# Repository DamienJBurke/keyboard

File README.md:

# keyboard
Repo for my keyboard Design schematic and pcb layout

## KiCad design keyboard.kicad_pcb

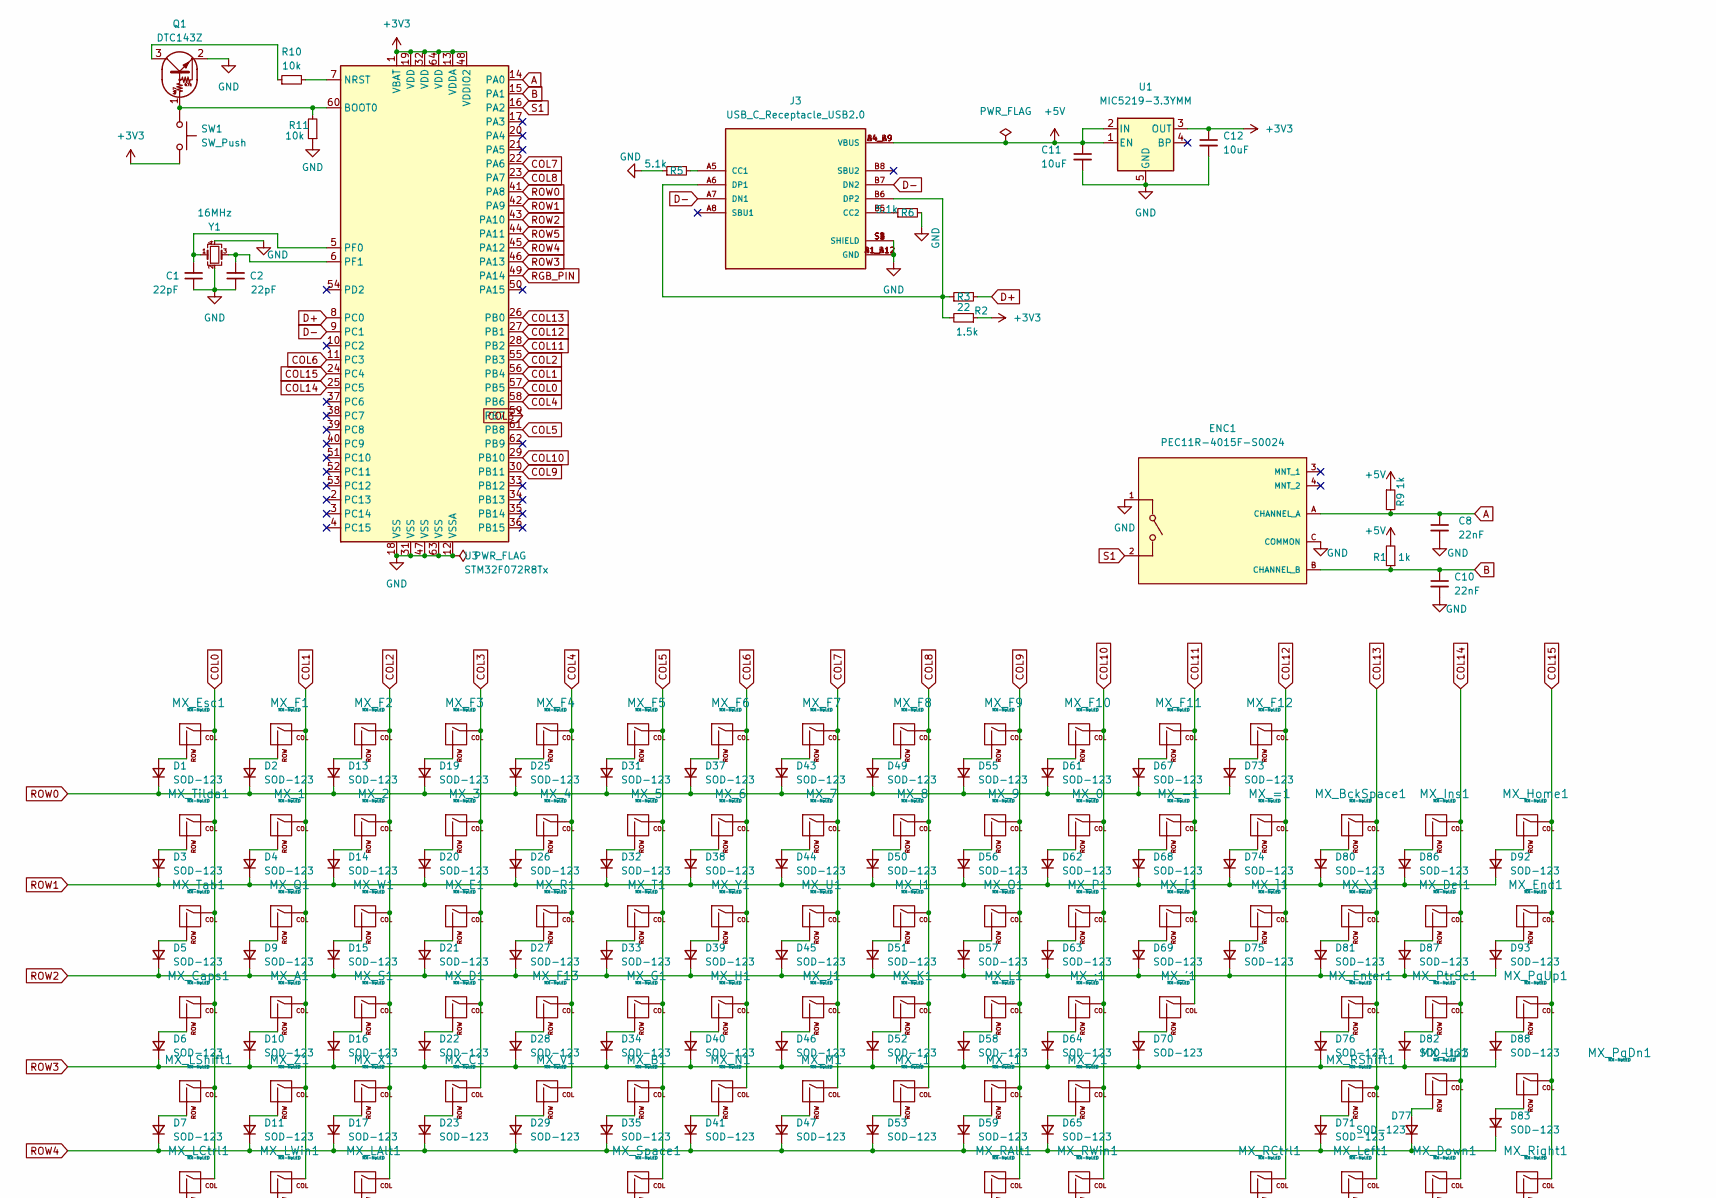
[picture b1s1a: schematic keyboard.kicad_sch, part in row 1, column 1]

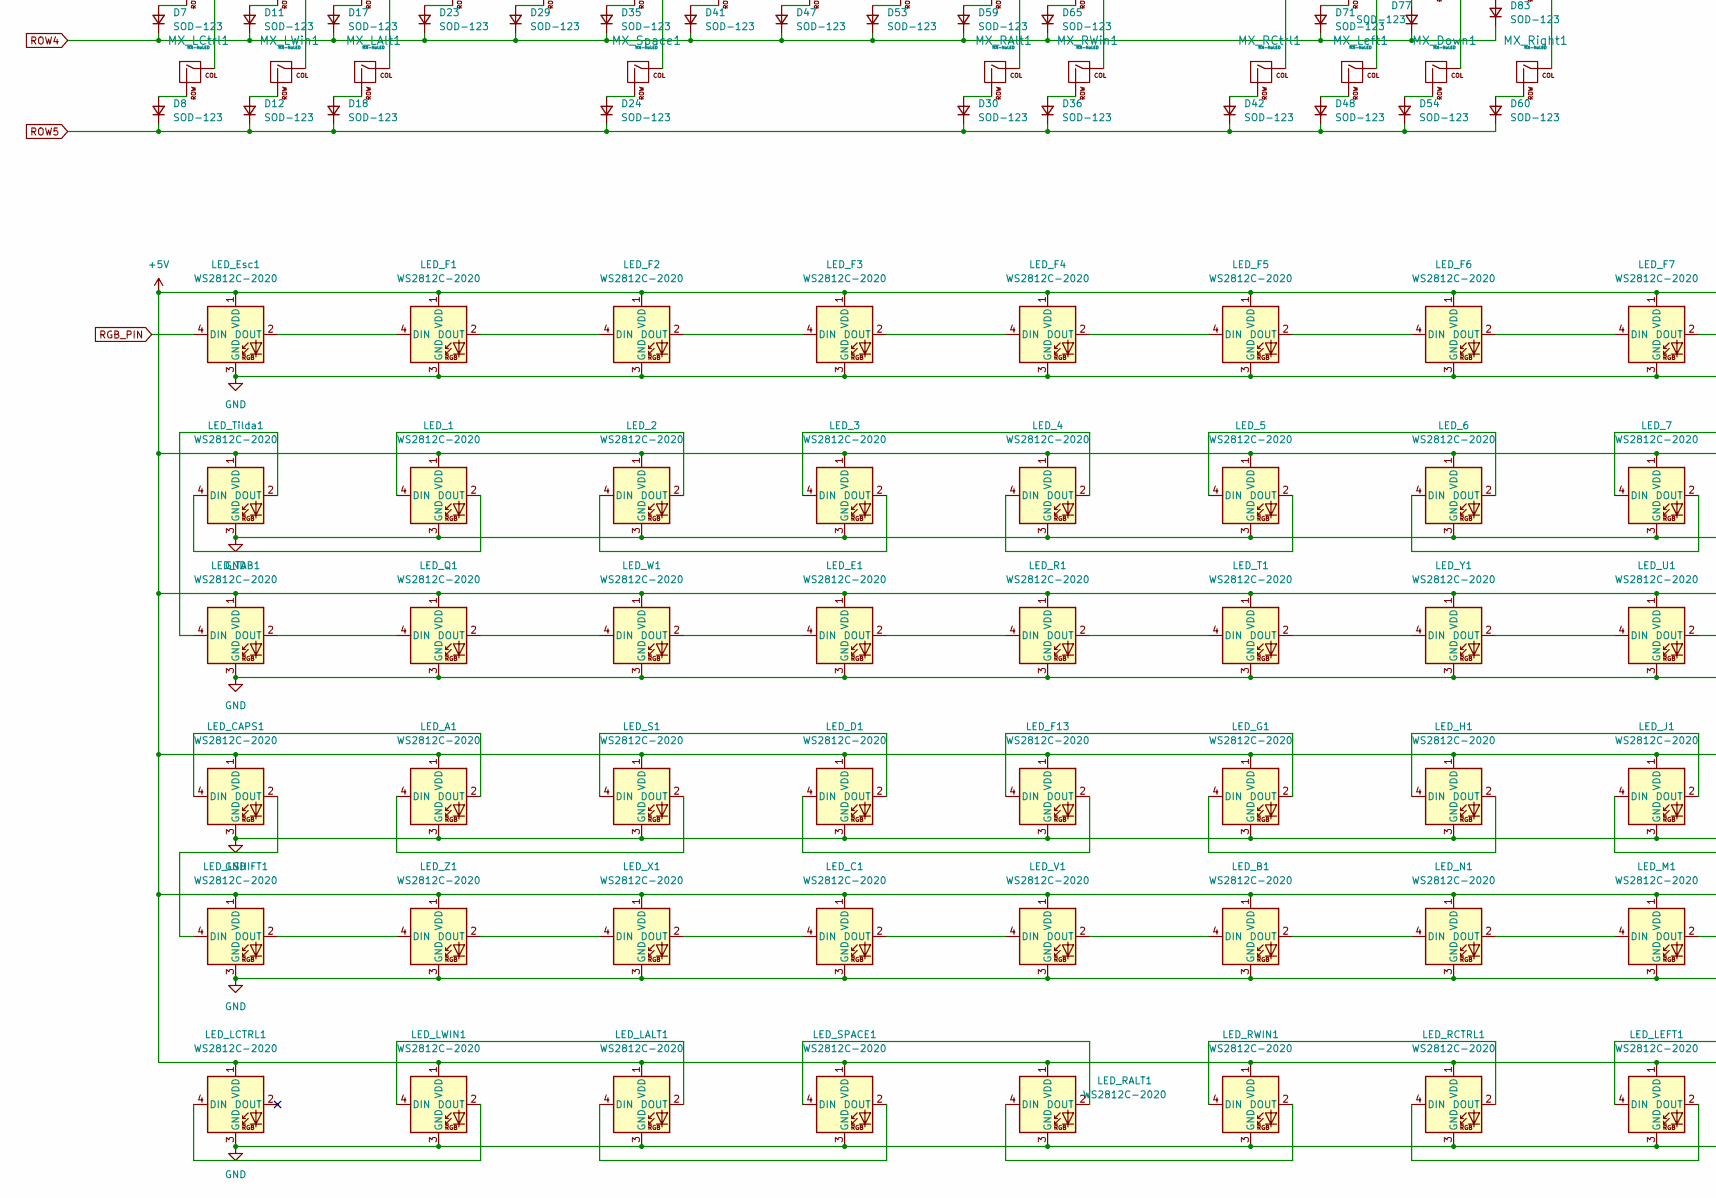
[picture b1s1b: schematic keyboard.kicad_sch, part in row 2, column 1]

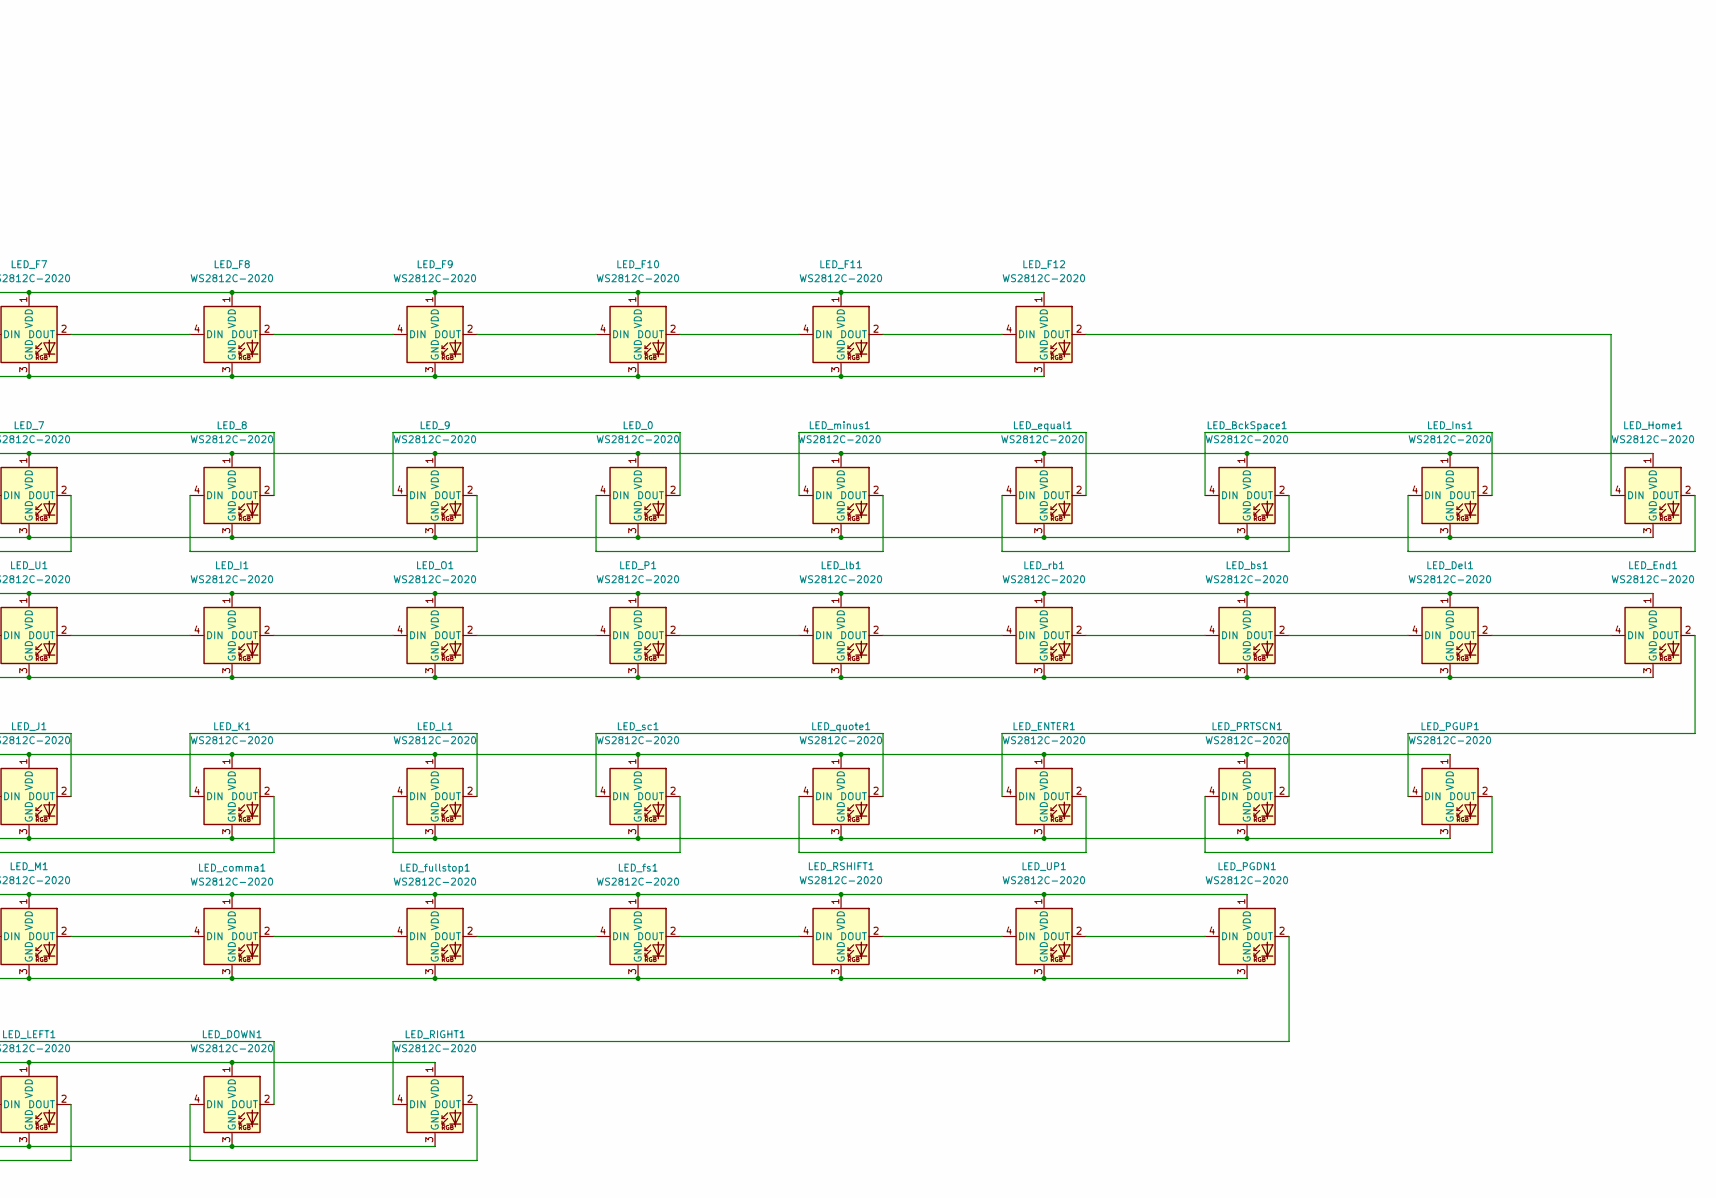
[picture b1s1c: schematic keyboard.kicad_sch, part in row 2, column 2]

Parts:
C1, C2: 22pF; C_0805_2012Metric
C8, C10: 22nF; C_0805_2012Metric
C11, C12: 10uF; C_0805_2012Metric
D1, D2, D3, D4, D5, D6, D7, D8, D9, D10, D11, D12, D13, D14, D15, D16, D17, D18, D19, D20, D21, D22, D23, D24, D25, D26, D27, D28, D29, D30, D31, D32, D33, D34, D35, D36, D37, D38, D39, D40, D41, D42, D43, D44, D45, D46, D47, D48, D49, D50, D51, D52, D53, D54, D55, D56, D57, D58, D59, D60, D61, D62, D63, D64, D65, D67, D68, D69, D70, D71, D73, D74, D75, D76, D77, D80, D81, D82, D83, D86, D87, D88, D92, D93: SOD-123; D_SOD-123
ENC1: PEC11R-4015F-S0024; XDCR_PEC11R-4215F-S0024; current rating 10mA; voltage rating DC 5V; mouser part number 652-PEC11R-4015F-S24; digikey description ROTARY ENCODER MECHANICAL 24PPR
J3: USB_C_Receptacle_USB2.0; HRO_TYPE-C-31-M-12; PARTREV 2020.12.08
LED_0, LED_1, LED_2, LED_3, LED_4, LED_5, LED_6, LED_7, LED_8, LED_9: WS2812C-2020; SK6812-MINI-E-CUSTOM; PARTREV V1.0
LED_A1: WS2812C-2020; SK6812-MINI-E-CUSTOM; PARTREV V1.0
LED_B1: WS2812C-2020; SK6812-MINI-E-CUSTOM; PARTREV V1.0
LED_BckSpace1: WS2812C-2020; SK6812-MINI-E-CUSTOM; PARTREV V1.0
LED_C1: WS2812C-2020; SK6812-MINI-E-CUSTOM; PARTREV V1.0
LED_CAPS1: WS2812C-2020; SK6812-MINI-E-CUSTOM; PARTREV V1.0
LED_D1: WS2812C-2020; SK6812-MINI-E-CUSTOM; PARTREV V1.0
LED_DOWN1: WS2812C-2020; SK6812-MINI-E-CUSTOM; PARTREV V1.0
LED_Del1: WS2812C-2020; SK6812-MINI-E-CUSTOM; PARTREV V1.0
LED_E1: WS2812C-2020; SK6812-MINI-E-CUSTOM; PARTREV V1.0
LED_ENTER1: WS2812C-2020; SK6812-MINI-E-CUSTOM; PARTREV V1.0
LED_End1: WS2812C-2020; SK6812-MINI-E-CUSTOM; PARTREV V1.0
LED_Esc1: WS2812C-2020; SK6812-MINI-E-CUSTOM; PARTREV V1.0
LED_F1, LED_F2, LED_F3, LED_F4, LED_F5, LED_F6, LED_F7, LED_F8, LED_F9, LED_F10, LED_F11, LED_F12, LED_F13: WS2812C-2020; SK6812-MINI-E-CUSTOM; PARTREV V1.0
LED_G1: WS2812C-2020; SK6812-MINI-E-CUSTOM; PARTREV V1.0
LED_H1: WS2812C-2020; SK6812-MINI-E-CUSTOM; PARTREV V1.0
LED_Home1: WS2812C-2020; SK6812-MINI-E-CUSTOM; PARTREV V1.0
LED_I1: WS2812C-2020; SK6812-MINI-E-CUSTOM; PARTREV V1.0
LED_Ins1: WS2812C-2020; SK6812-MINI-E-CUSTOM; PARTREV V1.0
LED_J1: WS2812C-2020; SK6812-MINI-E-CUSTOM; PARTREV V1.0
LED_K1: WS2812C-2020; SK6812-MINI-E-CUSTOM; PARTREV V1.0
LED_L1: WS2812C-2020; SK6812-MINI-E-CUSTOM; PARTREV V1.0
LED_LALT1: WS2812C-2020; SK6812-MINI-E-CUSTOM; PARTREV V1.0
LED_LCTRL1: WS2812C-2020; SK6812-MINI-E-CUSTOM; PARTREV V1.0
LED_LEFT1: WS2812C-2020; SK6812-MINI-E-CUSTOM; PARTREV V1.0
LED_LSHIFT1: WS2812C-2020; SK6812-MINI-E-CUSTOM; PARTREV V1.0
LED_LWIN1: WS2812C-2020; SK6812-MINI-E-CUSTOM; PARTREV V1.0
LED_M1: WS2812C-2020; SK6812-MINI-E-CUSTOM; PARTREV V1.0
LED_N1: WS2812C-2020; SK6812-MINI-E-CUSTOM; PARTREV V1.0
LED_O1: WS2812C-2020; SK6812-MINI-E-CUSTOM; PARTREV V1.0
LED_P1: WS2812C-2020; SK6812-MINI-E-CUSTOM; PARTREV V1.0
LED_PGDN1: WS2812C-2020; SK6812-MINI-E-CUSTOM; PARTREV V1.0
LED_PGUP1: WS2812C-2020; SK6812-MINI-E-CUSTOM; PARTREV V1.0
LED_PRTSCN1: WS2812C-2020; SK6812-MINI-E-CUSTOM; PARTREV V1.0
LED_Q1: WS2812C-2020; SK6812-MINI-E-CUSTOM; PARTREV V1.0
LED_R1: WS2812C-2020; SK6812-MINI-E-CUSTOM; PARTREV V1.0
LED_RALT1: WS2812C-2020; SK6812-MINI-E-CUSTOM; PARTREV V1.0
LED_RCTRL1: WS2812C-2020; SK6812-MINI-E-CUSTOM; PARTREV V1.0
LED_RIGHT1: WS2812C-2020; SK6812-MINI-E-CUSTOM; PARTREV V1.0
LED_RSHIFT1: WS2812C-2020; SK6812-MINI-E-CUSTOM; PARTREV V1.0
LED_RWIN1: WS2812C-2020; SK6812-MINI-E-CUSTOM; PARTREV V1.0
LED_S1: WS2812C-2020; SK6812-MINI-E-CUSTOM; PARTREV V1.0
LED_SPACE1: WS2812C-2020; SK6812-MINI-E-CUSTOM; PARTREV V1.0
LED_T1: WS2812C-2020; SK6812-MINI-E-CUSTOM; PARTREV V1.0
LED_TAB1: WS2812C-2020; SK6812-MINI-E-CUSTOM; PARTREV V1.0
LED_Tilda1: WS2812C-2020; SK6812-MINI-E-CUSTOM; PARTREV V1.0
LED_U1: WS2812C-2020; SK6812-MINI-E-CUSTOM; PARTREV V1.0
LED_UP1: WS2812C-2020; SK6812-MINI-E-CUSTOM; PARTREV V1.0
LED_V1: WS2812C-2020; SK6812-MINI-E-CUSTOM; PARTREV V1.0
LED_W1: WS2812C-2020; SK6812-MINI-E-CUSTOM; PARTREV V1.0
LED_X1: WS2812C-2020; SK6812-MINI-E-CUSTOM; PARTREV V1.0
LED_Y1: WS2812C-2020; SK6812-MINI-E-CUSTOM; PARTREV V1.0
LED_Z1: WS2812C-2020; SK6812-MINI-E-CUSTOM; PARTREV V1.0
LED_bs1: WS2812C-2020; SK6812-MINI-E-CUSTOM; PARTREV V1.0
LED_comma1: WS2812C-2020; SK6812-MINI-E-CUSTOM; PARTREV V1.0
LED_equal1: WS2812C-2020; SK6812-MINI-E-CUSTOM; PARTREV V1.0
LED_fs1: WS2812C-2020; SK6812-MINI-E-CUSTOM; PARTREV V1.0
LED_fullstop1: WS2812C-2020; SK6812-MINI-E-CUSTOM; PARTREV V1.0
LED_lb1: WS2812C-2020; SK6812-MINI-E-CUSTOM; PARTREV V1.0
LED_minus1: WS2812C-2020; SK6812-MINI-E-CUSTOM; PARTREV V1.0
LED_quote1: WS2812C-2020; SK6812-MINI-E-CUSTOM; PARTREV V1.0
LED_rb1: WS2812C-2020; SK6812-MINI-E-CUSTOM; PARTREV V1.0
LED_sc1: WS2812C-2020; SK6812-MINI-E-CUSTOM; PARTREV V1.0
MX_0, MX_1, MX_2, MX_3, MX_4, MX_5, MX_6, MX_7, MX_8, MX_9, MX_.1: MX-NoLED; SW_Cherry_MX_PCB_1.00u
MX_'1: MX-NoLED; SW_Cherry_MX_PCB_1.00u
MX_,1: MX-NoLED; SW_Cherry_MX_PCB_1.00u
MX_-1: MX-NoLED; SW_Cherry_MX_PCB_1.00u
MX_/1: MX-NoLED; SW_Cherry_MX_PCB_1.00u
MX_;1: MX-NoLED; SW_Cherry_MX_PCB_1.00u
MX_=1: MX-NoLED; SW_Cherry_MX_PCB_1.00u
MX_A1: MX-NoLED; SW_Cherry_MX_PCB_1.00u
MX_B1: MX-NoLED; SW_Cherry_MX_PCB_1.00u
MX_BckSpace1: MX-NoLED; Cherry 2u with stablizer
MX_C1: MX-NoLED; SW_Cherry_MX_PCB_1.00u
MX_Caps1: MX-NoLED; SW_Cherry_MX_PCB_1.75u
MX_D1: MX-NoLED; SW_Cherry_MX_PCB_1.00u
MX_Del1: MX-NoLED; SW_Cherry_MX_PCB_1.00u
MX_Down1: MX-NoLED; SW_Cherry_MX_PCB_1.00u
MX_E1: MX-NoLED; SW_Cherry_MX_PCB_1.00u
MX_End1: MX-NoLED; SW_Cherry_MX_PCB_1.00u
MX_Enter1: MX-NoLED; Cherry 2.25 with stablizer
MX_Esc1: MX-NoLED; SW_Cherry_MX_PCB_1.00u
MX_F1, MX_F2, MX_F3, MX_F4, MX_F5, MX_F6, MX_F7, MX_F8, MX_F9, MX_F10, MX_F11, MX_F12, MX_F13: MX-NoLED; SW_Cherry_MX_PCB_1.00u
MX_G1: MX-NoLED; SW_Cherry_MX_PCB_1.00u
MX_H1: MX-NoLED; SW_Cherry_MX_PCB_1.00u
MX_Home1: MX-NoLED; SW_Cherry_MX_PCB_1.00u
MX_I1: MX-NoLED; SW_Cherry_MX_PCB_1.00u
MX_Ins1: MX-NoLED; SW_Cherry_MX_PCB_1.00u
MX_J1: MX-NoLED; SW_Cherry_MX_PCB_1.00u
MX_K1: MX-NoLED; SW_Cherry_MX_PCB_1.00u
MX_L1: MX-NoLED; SW_Cherry_MX_PCB_1.00u
MX_LAlt1: MX-NoLED; SW_Cherry_MX_PCB_1.25u
MX_LCtrl1: MX-NoLED; SW_Cherry_MX_PCB_1.25u
MX_LShift1: MX-NoLED; Cherry 2.25 with stablizer
MX_LWin1: MX-NoLED; SW_Cherry_MX_PCB_1.25u
MX_Left1: MX-NoLED; SW_Cherry_MX_PCB_1.00u
MX_M1: MX-NoLED; SW_Cherry_MX_PCB_1.00u
MX_N1: MX-NoLED; SW_Cherry_MX_PCB_1.00u
MX_O1: MX-NoLED; SW_Cherry_MX_PCB_1.00u
MX_P1: MX-NoLED; SW_Cherry_MX_PCB_1.00u
MX_PgDn1: MX-NoLED; SW_Cherry_MX_PCB_1.00u
MX_PgUp1: MX-NoLED; SW_Cherry_MX_PCB_1.00u
MX_PtrSc1: MX-NoLED; SW_Cherry_MX_PCB_1.00u
MX_Q1: MX-NoLED; SW_Cherry_MX_PCB_1.00u
MX_R1: MX-NoLED; SW_Cherry_MX_PCB_1.00u
MX_RAlt1: MX-NoLED; SW_Cherry_MX_PCB_1.25u
MX_RCtrl1: MX-NoLED; SW_Cherry_MX_PCB_1.25u
MX_RShift1: MX-NoLED; Cherry 2.75 with stablizer
MX_RWin1: MX-NoLED; SW_Cherry_MX_PCB_1.25u
MX_Right1: MX-NoLED; SW_Cherry_MX_PCB_1.00u
MX_S1: MX-NoLED; SW_Cherry_MX_PCB_1.00u
MX_Space1: MX-NoLED; Cherry 6u with upside down Stablizer
MX_T1: MX-NoLED; SW_Cherry_MX_PCB_1.00u
MX_Tab1: MX-NoLED; SW_Cherry_MX_PCB_1.50u
MX_Tilda1: MX-NoLED; SW_Cherry_MX_PCB_1.00u
MX_U1: MX-NoLED; SW_Cherry_MX_PCB_1.00u
MX_Up1: MX-NoLED; SW_Cherry_MX_PCB_1.00u
MX_V1: MX-NoLED; SW_Cherry_MX_PCB_1.00u
MX_W1: MX-NoLED; SW_Cherry_MX_PCB_1.00u
MX_X1: MX-NoLED; SW_Cherry_MX_PCB_1.00u
MX_Y1: MX-NoLED; SW_Cherry_MX_PCB_1.00u
MX_Z1: MX-NoLED; SW_Cherry_MX_PCB_1.00u
MX_[1: MX-NoLED; SW_Cherry_MX_PCB_1.00u
MX_\1: MX-NoLED; SW_Cherry_MX_PCB_1.50u
MX_]1: MX-NoLED; SW_Cherry_MX_PCB_1.00u
Q1: DTC143Z; SOTFL3P40_120X120X55L30X32N
R1, R9: 1k; R_0805_2012Metric
R2: 1.5k; R_0805_2012Metric
R3: 22; R_0805_2012Metric
R5, R6: 5.1k; R_0805_2012Metric
R10, R11: 10k; R_0805_2012Metric
SW1: SW_Push; SKQG-1155865
U1: MIC5219-3.3YMM; SOP65P490X110-8N
U3: STM32F072R8Tx; LQFP-64_10x10mm_P0.5mm
Y1: 16MHz; Crystal_SMD_3225-4Pin_3.2x2.5mm

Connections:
+3V3: C12.1, R2.1, SW1.2, U1.3 (OUT), U3.1 (VBAT), U3.13 (VDDA), U3.19 (VDD), U3.32 (VDD), U3.48 (VDDIO2), U3.64 (VDD)
+5V: C11.1, J3.A4_B9 (VBUS), J3.B4_A9 (VBUS), LED_0.1 (VDD), LED_1.1 (VDD), LED_2.1 (VDD), LED_3.1 (VDD), LED_4.1 (VDD), LED_5.1 (VDD), LED_6.1 (VDD), LED_7.1 (VDD), LED_8.1 (VDD), LED_9.1 (VDD), LED_A1.1 (VDD), LED_B1.1 (VDD), LED_BckSpace1.1 (VDD), LED_C1.1 (VDD), LED_CAPS1.1 (VDD), LED_D1.1 (VDD), LED_DOWN1.1 (VDD), LED_Del1.1 (VDD), LED_E1.1 (VDD), LED_ENTER1.1 (VDD), LED_End1.1 (VDD), LED_Esc1.1 (VDD), LED_F1.1 (VDD), LED_F2.1 (VDD), LED_F3.1 (VDD), LED_F4.1 (VDD), LED_F5.1 (VDD), LED_F6.1 (VDD), LED_F7.1 (VDD), LED_F8.1 (VDD), LED_F9.1 (VDD), LED_F10.1 (VDD), LED_F11.1 (VDD), LED_F12.1 (VDD), LED_F13.1 (VDD), LED_G1.1 (VDD), LED_H1.1 (VDD), LED_Home1.1 (VDD), LED_I1.1 (VDD), LED_Ins1.1 (VDD), LED_J1.1 (VDD), LED_K1.1 (VDD), LED_L1.1 (VDD), LED_LALT1.1 (VDD), LED_LCTRL1.1 (VDD), LED_LEFT1.1 (VDD), LED_LSHIFT1.1 (VDD), LED_LWIN1.1 (VDD), LED_M1.1 (VDD), LED_N1.1 (VDD), LED_O1.1 (VDD), LED_P1.1 (VDD), LED_PGDN1.1 (VDD), LED_PGUP1.1 (VDD), LED_PRTSCN1.1 (VDD), LED_Q1.1 (VDD), LED_R1.1 (VDD), LED_RALT1.1 (VDD), LED_RCTRL1.1 (VDD), LED_RIGHT1.1 (VDD), LED_RSHIFT1.1 (VDD), LED_RWIN1.1 (VDD), LED_S1.1 (VDD), LED_SPACE1.1 (VDD), LED_T1.1 (VDD), LED_TAB1.1 (VDD), LED_Tilda1.1 (VDD), LED_U1.1 (VDD), LED_UP1.1 (VDD), LED_V1.1 (VDD), LED_W1.1 (VDD), LED_X1.1 (VDD), LED_Y1.1 (VDD), LED_Z1.1 (VDD), LED_bs1.1 (VDD), LED_comma1.1 (VDD), LED_equal1.1 (VDD), LED_fs1.1 (VDD), LED_fullstop1.1 (VDD), LED_lb1.1 (VDD), LED_minus1.1 (VDD), LED_quote1.1 (VDD), LED_rb1.1 (VDD), LED_sc1.1 (VDD), R1.2, R9.1, U1.1 (EN), U1.2 (IN)
A: C8.1, ENC1.A (CHANNEL_A), R9.2, U3.14 (PA0)
B: C10.1, ENC1.B (CHANNEL_B), R1.1, U3.15 (PA1)
COL0: MX_Caps1.1 (COL), MX_Esc1.1 (COL), MX_LCtrl1.1 (COL), MX_LShift1.1 (COL), MX_Tab1.1 (COL), MX_Tilda1.1 (COL), U3.57 (PB5)
COL1: MX_1.1 (COL), MX_A1.1 (COL), MX_F1.1 (COL), MX_LWin1.1 (COL), MX_Q1.1 (COL), MX_Z1.1 (COL), U3.56 (PB4)
COL2: MX_2.1 (COL), MX_F2.1 (COL), MX_LAlt1.1 (COL), MX_S1.1 (COL), MX_W1.1 (COL), MX_X1.1 (COL), U3.55 (PB3)
COL3: MX_3.1 (COL), MX_C1.1 (COL), MX_D1.1 (COL), MX_E1.1 (COL), MX_F3.1 (COL), U3.59 (PB7)
COL4: MX_4.1 (COL), MX_F4.1 (COL), MX_F13.1 (COL), MX_R1.1 (COL), MX_V1.1 (COL), U3.58 (PB6)
COL5: MX_5.1 (COL), MX_B1.1 (COL), MX_F5.1 (COL), MX_G1.1 (COL), MX_Space1.1 (COL), MX_T1.1 (COL), U3.61 (PB8)
COL6: MX_6.1 (COL), MX_F6.1 (COL), MX_H1.1 (COL), MX_N1.1 (COL), MX_Y1.1 (COL), U3.11 (PC3)
COL7: MX_7.1 (COL), MX_F7.1 (COL), MX_J1.1 (COL), MX_M1.1 (COL), MX_U1.1 (COL), U3.22 (PA6)
COL8: MX_8.1 (COL), MX_,1.1 (COL), MX_F8.1 (COL), MX_I1.1 (COL), MX_K1.1 (COL), U3.23 (PA7)
COL9: MX_9.1 (COL), MX_.1.1 (COL), MX_F9.1 (COL), MX_L1.1 (COL), MX_O1.1 (COL), MX_RAlt1.1 (COL), U3.30 (PB11)
COL10: MX_0.1 (COL), MX_/1.1 (COL), MX_;1.1 (COL), MX_F10.1 (COL), MX_P1.1 (COL), MX_RWin1.1 (COL), U3.29 (PB10)
COL11: MX_'1.1 (COL), MX_-1.1 (COL), MX_F11.1 (COL), MX_[1.1 (COL), U3.28 (PB2)
COL12: MX_=1.1 (COL), MX_F12.1 (COL), MX_RCtrl1.1 (COL), MX_]1.1 (COL), U3.27 (PB1)
COL13: MX_BckSpace1.1 (COL), MX_Enter1.1 (COL), MX_Left1.1 (COL), MX_RShift1.1 (COL), MX_\1.1 (COL), U3.26 (PB0)
COL14: MX_Del1.1 (COL), MX_Down1.1 (COL), MX_Ins1.1 (COL), MX_PtrSc1.1 (COL), MX_Up1.1 (COL), U3.25 (PC5)
COL15: MX_End1.1 (COL), MX_Home1.1 (COL), MX_PgDn1.1 (COL), MX_PgUp1.1 (COL), MX_Right1.1 (COL), U3.24 (PC4)
D+: R3.2, U3.8 (PC0)
D-: J3.A7 (DN1), J3.B7 (DN2), U3.9 (PC1)
GND: C1.1, C2.1, C8.2, C10.2, C11.2, C12.2, ENC1.1, ENC1.C (COMMON), J3.A1_B12 (GND), J3.B1_A12 (GND), J3.S1 (SHIELD), J3.S2 (SHIELD), J3.S3 (SHIELD), J3.S4 (SHIELD), LED_0.3 (GND), LED_1.3 (GND), LED_2.3 (GND), LED_3.3 (GND), LED_4.3 (GND), LED_5.3 (GND), LED_6.3 (GND), LED_7.3 (GND), LED_8.3 (GND), LED_9.3 (GND), LED_A1.3 (GND), LED_B1.3 (GND), LED_BckSpace1.3 (GND), LED_C1.3 (GND), LED_CAPS1.3 (GND), LED_D1.3 (GND), LED_DOWN1.3 (GND), LED_Del1.3 (GND), LED_E1.3 (GND), LED_ENTER1.3 (GND), LED_End1.3 (GND), LED_Esc1.3 (GND), LED_F1.3 (GND), LED_F2.3 (GND), LED_F3.3 (GND), LED_F4.3 (GND), LED_F5.3 (GND), LED_F6.3 (GND), LED_F7.3 (GND), LED_F8.3 (GND), LED_F9.3 (GND), LED_F10.3 (GND), LED_F11.3 (GND), LED_F12.3 (GND), LED_F13.3 (GND), LED_G1.3 (GND), LED_H1.3 (GND), LED_Home1.3 (GND), LED_I1.3 (GND), LED_Ins1.3 (GND), LED_J1.3 (GND), LED_K1.3 (GND), LED_L1.3 (GND), LED_LALT1.3 (GND), LED_LCTRL1.3 (GND), LED_LEFT1.3 (GND), LED_LSHIFT1.3 (GND), LED_LWIN1.3 (GND), LED_M1.3 (GND), LED_N1.3 (GND), LED_O1.3 (GND), LED_P1.3 (GND), LED_PGDN1.3 (GND), LED_PGUP1.3 (GND), LED_PRTSCN1.3 (GND), LED_Q1.3 (GND), LED_R1.3 (GND), LED_RALT1.3 (GND), LED_RCTRL1.3 (GND), LED_RIGHT1.3 (GND), LED_RSHIFT1.3 (GND), LED_RWIN1.3 (GND), LED_S1.3 (GND), LED_SPACE1.3 (GND), LED_T1.3 (GND), LED_TAB1.3 (GND), LED_Tilda1.3 (GND), LED_U1.3 (GND), LED_UP1.3 (GND), LED_V1.3 (GND), LED_W1.3 (GND), LED_X1.3 (GND), LED_Y1.3 (GND), LED_Z1.3 (GND), LED_bs1.3 (GND), LED_comma1.3 (GND), LED_equal1.3 (GND), LED_fs1.3 (GND), LED_fullstop1.3 (GND), LED_lb1.3 (GND), LED_minus1.3 (GND), LED_quote1.3 (GND), LED_rb1.3 (GND), LED_sc1.3 (GND), Q1.2 (E), R5.1, R6.2, R11.1, U1.5 (GND), U1.6 (GND), U1.7 (GND), U1.8 (GND), U3.12 (VSSA), U3.18 (VSS), U3.31 (VSS), U3.47 (VSS), U3.63 (VSS), Y1.2, Y1.4
unnamed: D1.2 (A), MX_Esc1.2 (ROW)
unnamed: D2.2 (A), MX_F1.2 (ROW)
unnamed: D3.2 (A), MX_Tilda1.2 (ROW)
unnamed: D4.2 (A), MX_1.2 (ROW)
unnamed: D5.2 (A), MX_Tab1.2 (ROW)
unnamed: D6.2 (A), MX_Caps1.2 (ROW)
unnamed: D7.2 (A), MX_LShift1.2 (ROW)
unnamed: D8.2 (A), MX_LCtrl1.2 (ROW)
unnamed: D9.2 (A), MX_Q1.2 (ROW)
unnamed: D10.2 (A), MX_A1.2 (ROW)
unnamed: D11.2 (A), MX_Z1.2 (ROW)
unnamed: D12.2 (A), MX_LWin1.2 (ROW)
unnamed: D13.2 (A), MX_F2.2 (ROW)
unnamed: D14.2 (A), MX_2.2 (ROW)
unnamed: D15.2 (A), MX_W1.2 (ROW)
unnamed: D16.2 (A), MX_S1.2 (ROW)
unnamed: D17.2 (A), MX_X1.2 (ROW)
unnamed: D18.2 (A), MX_LAlt1.2 (ROW)
unnamed: D19.2 (A), MX_F3.2 (ROW)
unnamed: D20.2 (A), MX_3.2 (ROW)
unnamed: D21.2 (A), MX_E1.2 (ROW)
unnamed: D22.2 (A), MX_D1.2 (ROW)
unnamed: D23.2 (A), MX_C1.2 (ROW)
unnamed: D24.2 (A), MX_Space1.2 (ROW)
unnamed: D25.2 (A), MX_F4.2 (ROW)
unnamed: D26.2 (A), MX_4.2 (ROW)
unnamed: D27.2 (A), MX_R1.2 (ROW)
unnamed: D28.2 (A), MX_F13.2 (ROW)
unnamed: D29.2 (A), MX_V1.2 (ROW)
unnamed: D30.2 (A), MX_RAlt1.2 (ROW)
unnamed: D31.2 (A), MX_F5.2 (ROW)
unnamed: D32.2 (A), MX_5.2 (ROW)
unnamed: D33.2 (A), MX_T1.2 (ROW)
unnamed: D34.2 (A), MX_G1.2 (ROW)
unnamed: D35.2 (A), MX_B1.2 (ROW)
unnamed: D36.2 (A), MX_RWin1.2 (ROW)
unnamed: D37.2 (A), MX_F6.2 (ROW)
unnamed: D38.2 (A), MX_6.2 (ROW)
unnamed: D39.2 (A), MX_Y1.2 (ROW)
unnamed: D40.2 (A), MX_H1.2 (ROW)
unnamed: D41.2 (A), MX_N1.2 (ROW)
unnamed: D42.2 (A), MX_RCtrl1.2 (ROW)
unnamed: D43.2 (A), MX_F7.2 (ROW)
unnamed: D44.2 (A), MX_7.2 (ROW)
unnamed: D45.2 (A), MX_U1.2 (ROW)
unnamed: D46.2 (A), MX_J1.2 (ROW)
unnamed: D47.2 (A), MX_M1.2 (ROW)
unnamed: D48.2 (A), MX_Left1.2 (ROW)
unnamed: D49.2 (A), MX_F8.2 (ROW)
unnamed: D50.2 (A), MX_8.2 (ROW)
unnamed: D51.2 (A), MX_I1.2 (ROW)
unnamed: D52.2 (A), MX_K1.2 (ROW)
unnamed: D53.2 (A), MX_,1.2 (ROW)
unnamed: D54.2 (A), MX_Down1.2 (ROW)
unnamed: D55.2 (A), MX_F9.2 (ROW)
unnamed: D56.2 (A), MX_9.2 (ROW)
unnamed: D57.2 (A), MX_O1.2 (ROW)
unnamed: D58.2 (A), MX_L1.2 (ROW)
unnamed: D59.2 (A), MX_.1.2 (ROW)
unnamed: D60.2 (A), MX_Right1.2 (ROW)
unnamed: D61.2 (A), MX_F10.2 (ROW)
unnamed: D62.2 (A), MX_0.2 (ROW)
unnamed: D63.2 (A), MX_P1.2 (ROW)
unnamed: D64.2 (A), MX_;1.2 (ROW)
unnamed: D65.2 (A), MX_/1.2 (ROW)
unnamed: D67.2 (A), MX_F11.2 (ROW)
unnamed: D68.2 (A), MX_-1.2 (ROW)
unnamed: D69.2 (A), MX_[1.2 (ROW)
unnamed: D70.2 (A), MX_'1.2 (ROW)
unnamed: D71.2 (A), MX_RShift1.2 (ROW)
unnamed: D73.2 (A), MX_F12.2 (ROW)
unnamed: D74.2 (A), MX_=1.2 (ROW)
unnamed: D75.2 (A), MX_]1.2 (ROW)
unnamed: D76.2 (A), MX_Enter1.2 (ROW)
unnamed: D77.2 (A), MX_Up1.2 (ROW)
unnamed: D80.2 (A), MX_BckSpace1.2 (ROW)
unnamed: D81.2 (A), MX_\1.2 (ROW)
unnamed: D82.2 (A), MX_PtrSc1.2 (ROW)
unnamed: D83.2 (A), MX_PgDn1.2 (ROW)
unnamed: D86.2 (A), MX_Ins1.2 (ROW)
unnamed: D87.2 (A), MX_Del1.2 (ROW)
unnamed: D88.2 (A), MX_PgUp1.2 (ROW)
unnamed: D92.2 (A), MX_Home1.2 (ROW)
unnamed: D93.2 (A), MX_End1.2 (ROW)
unnamed: J3.A5 (CC1), R5.2
unnamed: J3.B5 (CC2), R6.1
unnamed: J3.A6 (DP1), J3.B6 (DP2), R2.2, R3.1
unnamed: LED_0.4 (DIN), LED_minus1.2 (DOUT)
unnamed: LED_0.2 (DOUT), LED_9.4 (DIN)
unnamed: LED_1.4 (DIN), LED_2.2 (DOUT)
unnamed: LED_1.2 (DOUT), LED_Tilda1.4 (DIN)
unnamed: LED_2.4 (DIN), LED_3.2 (DOUT)
unnamed: LED_3.4 (DIN), LED_4.2 (DOUT)
unnamed: LED_4.4 (DIN), LED_5.2 (DOUT)
unnamed: LED_5.4 (DIN), LED_6.2 (DOUT)
unnamed: LED_6.4 (DIN), LED_7.2 (DOUT)
unnamed: LED_7.4 (DIN), LED_8.2 (DOUT)
unnamed: LED_8.4 (DIN), LED_9.2 (DOUT)
unnamed: LED_A1.4 (DIN), LED_S1.2 (DOUT)
unnamed: LED_A1.2 (DOUT), LED_CAPS1.4 (DIN)
unnamed: LED_B1.4 (DIN), LED_V1.2 (DOUT)
unnamed: LED_B1.2 (DOUT), LED_N1.4 (DIN)
unnamed: LED_BckSpace1.4 (DIN), LED_Ins1.2 (DOUT)
unnamed: LED_BckSpace1.2 (DOUT), LED_equal1.4 (DIN)
unnamed: LED_C1.4 (DIN), LED_X1.2 (DOUT)
unnamed: LED_C1.2 (DOUT), LED_V1.4 (DIN)
unnamed: LED_CAPS1.2 (DOUT), LED_LSHIFT1.4 (DIN)
unnamed: LED_D1.4 (DIN), LED_F13.2 (DOUT)
unnamed: LED_D1.2 (DOUT), LED_S1.4 (DIN)
unnamed: LED_DOWN1.4 (DIN), LED_RIGHT1.2 (DOUT)
unnamed: LED_DOWN1.2 (DOUT), LED_LEFT1.4 (DIN)
unnamed: LED_Del1.4 (DIN), LED_bs1.2 (DOUT)
unnamed: LED_Del1.2 (DOUT), LED_End1.4 (DIN)
unnamed: LED_E1.4 (DIN), LED_W1.2 (DOUT)
unnamed: LED_E1.2 (DOUT), LED_R1.4 (DIN)
unnamed: LED_ENTER1.4 (DIN), LED_PRTSCN1.2 (DOUT)
unnamed: LED_ENTER1.2 (DOUT), LED_quote1.4 (DIN)
unnamed: LED_End1.2 (DOUT), LED_PGUP1.4 (DIN)
unnamed: LED_Esc1.2 (DOUT), LED_F1.4 (DIN)
unnamed: LED_F1.2 (DOUT), LED_F2.4 (DIN)
unnamed: LED_F2.2 (DOUT), LED_F3.4 (DIN)
unnamed: LED_F3.2 (DOUT), LED_F4.4 (DIN)
unnamed: LED_F4.2 (DOUT), LED_F5.4 (DIN)
unnamed: LED_F5.2 (DOUT), LED_F6.4 (DIN)
unnamed: LED_F6.2 (DOUT), LED_F7.4 (DIN)
unnamed: LED_F7.2 (DOUT), LED_F8.4 (DIN)
unnamed: LED_F8.2 (DOUT), LED_F9.4 (DIN)
unnamed: LED_F9.2 (DOUT), LED_F10.4 (DIN)
unnamed: LED_F10.2 (DOUT), LED_F11.4 (DIN)
unnamed: LED_F11.2 (DOUT), LED_F12.4 (DIN)
unnamed: LED_F12.2 (DOUT), LED_Home1.4 (DIN)
unnamed: LED_F13.4 (DIN), LED_G1.2 (DOUT)
unnamed: LED_G1.4 (DIN), LED_H1.2 (DOUT)
unnamed: LED_H1.4 (DIN), LED_J1.2 (DOUT)
unnamed: LED_Home1.2 (DOUT), LED_Ins1.4 (DIN)
unnamed: LED_I1.4 (DIN), LED_U1.2 (DOUT)
unnamed: LED_I1.2 (DOUT), LED_O1.4 (DIN)
unnamed: LED_J1.4 (DIN), LED_K1.2 (DOUT)
unnamed: LED_K1.4 (DIN), LED_L1.2 (DOUT)
unnamed: LED_L1.4 (DIN), LED_sc1.2 (DOUT)
unnamed: LED_LALT1.4 (DIN), LED_SPACE1.2 (DOUT)
unnamed: LED_LALT1.2 (DOUT), LED_LWIN1.4 (DIN)
unnamed: LED_LCTRL1.4 (DIN), LED_LWIN1.2 (DOUT)
unnamed: LED_LEFT1.2 (DOUT), LED_RCTRL1.4 (DIN)
unnamed: LED_LSHIFT1.2 (DOUT), LED_Z1.4 (DIN)
unnamed: LED_M1.4 (DIN), LED_N1.2 (DOUT)
unnamed: LED_M1.2 (DOUT), LED_comma1.4 (DIN)
unnamed: LED_O1.2 (DOUT), LED_P1.4 (DIN)
unnamed: LED_P1.2 (DOUT), LED_lb1.4 (DIN)
unnamed: LED_PGDN1.4 (DIN), LED_UP1.2 (DOUT)
unnamed: LED_PGDN1.2 (DOUT), LED_RIGHT1.4 (DIN)
unnamed: LED_PGUP1.2 (DOUT), LED_PRTSCN1.4 (DIN)
unnamed: LED_Q1.4 (DIN), LED_TAB1.2 (DOUT)
unnamed: LED_Q1.2 (DOUT), LED_W1.4 (DIN)
unnamed: LED_R1.2 (DOUT), LED_T1.4 (DIN)
unnamed: LED_RALT1.4 (DIN), LED_RWIN1.2 (DOUT)
unnamed: LED_RALT1.2 (DOUT), LED_SPACE1.4 (DIN)
unnamed: LED_RCTRL1.2 (DOUT), LED_RWIN1.4 (DIN)
unnamed: LED_RSHIFT1.4 (DIN), LED_fs1.2 (DOUT)
unnamed: LED_RSHIFT1.2 (DOUT), LED_UP1.4 (DIN)
unnamed: LED_T1.2 (DOUT), LED_Y1.4 (DIN)
unnamed: LED_TAB1.4 (DIN), LED_Tilda1.2 (DOUT)
unnamed: LED_U1.4 (DIN), LED_Y1.2 (DOUT)
unnamed: LED_X1.4 (DIN), LED_Z1.2 (DOUT)
unnamed: LED_bs1.4 (DIN), LED_rb1.2 (DOUT)
unnamed: LED_comma1.2 (DOUT), LED_fullstop1.4 (DIN)
unnamed: LED_equal1.2 (DOUT), LED_minus1.4 (DIN)
unnamed: LED_fs1.4 (DIN), LED_fullstop1.2 (DOUT)
unnamed: LED_lb1.2 (DOUT), LED_rb1.4 (DIN)
unnamed: LED_quote1.2 (DOUT), LED_sc1.4 (DIN)
unnamed: Q1.1 (B), R11.2, SW1.1, U3.60 (BOOT0)
unnamed: Q1.3 (C), R10.1
unnamed: R10.2, U3.7 (NRST)
unnamed: C1.2, U3.5 (PF0), Y1.1
unnamed: C2.2, U3.6 (PF1), Y1.3
RGB_PIN: LED_Esc1.4 (DIN), U3.49 (PA14)
ROW0: D1.1 (K), D2.1 (K), D13.1 (K), D19.1 (K), D25.1 (K), D31.1 (K), D37.1 (K), D43.1 (K), D49.1 (K), D55.1 (K), D61.1 (K), D67.1 (K), D73.1 (K), U3.41 (PA8)
ROW1: D3.1 (K), D4.1 (K), D14.1 (K), D20.1 (K), D26.1 (K), D32.1 (K), D38.1 (K), D44.1 (K), D50.1 (K), D56.1 (K), D62.1 (K), D68.1 (K), D74.1 (K), D80.1 (K), D86.1 (K), D92.1 (K), U3.42 (PA9)
ROW2: D5.1 (K), D9.1 (K), D15.1 (K), D21.1 (K), D27.1 (K), D33.1 (K), D39.1 (K), D45.1 (K), D51.1 (K), D57.1 (K), D63.1 (K), D69.1 (K), D75.1 (K), D81.1 (K), D87.1 (K), D93.1 (K), U3.43 (PA10)
ROW3: D6.1 (K), D10.1 (K), D16.1 (K), D22.1 (K), D28.1 (K), D34.1 (K), D40.1 (K), D46.1 (K), D52.1 (K), D58.1 (K), D64.1 (K), D70.1 (K), D76.1 (K), D82.1 (K), D88.1 (K), U3.46 (PA13)
ROW4: D7.1 (K), D11.1 (K), D17.1 (K), D23.1 (K), D29.1 (K), D35.1 (K), D41.1 (K), D47.1 (K), D53.1 (K), D59.1 (K), D65.1 (K), D71.1 (K), D77.1 (K), D83.1 (K), U3.45 (PA12)
ROW5: D8.1 (K), D12.1 (K), D18.1 (K), D24.1 (K), D30.1 (K), D36.1 (K), D42.1 (K), D48.1 (K), D54.1 (K), D60.1 (K), U3.44 (PA11)
S1: ENC1.2, U3.16 (PA2)

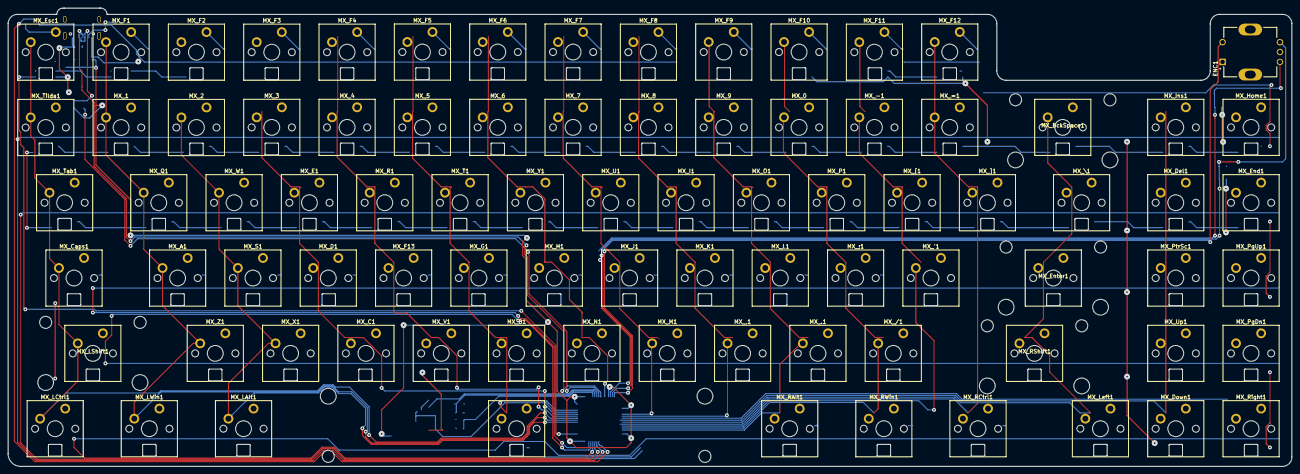
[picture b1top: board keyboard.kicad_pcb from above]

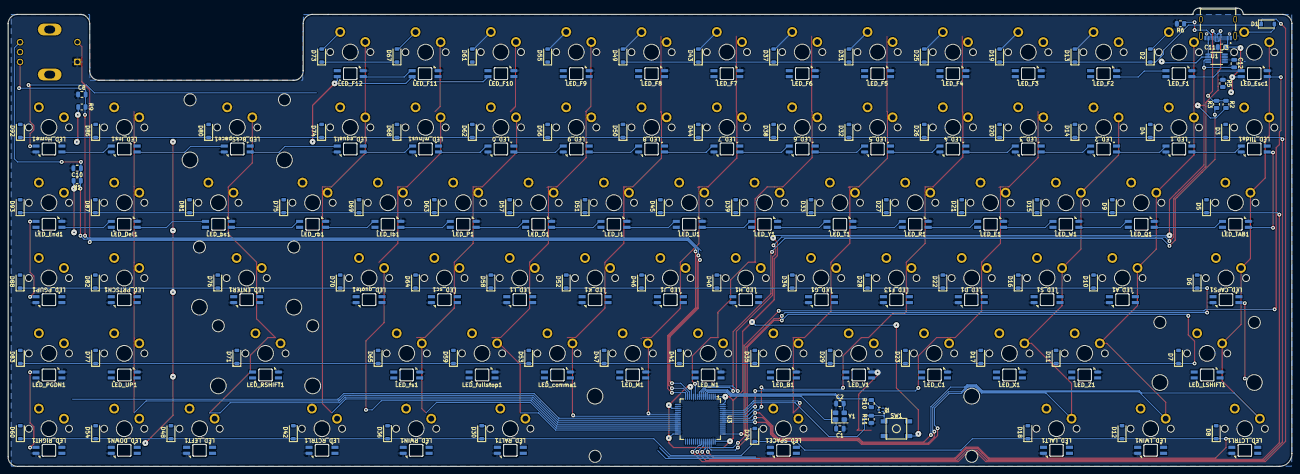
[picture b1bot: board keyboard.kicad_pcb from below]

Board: 2 copper layers, 324.6 x 115.9 mm, 273 parts (188 on the bottom side), 206 nets.

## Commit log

2025-09-08 Migrate project to keyboartd repo
2025-09-15 fixed led for minus with custom footprint
2025-09-17 Updated footprints, still need to do usb
2025-09-17 Updated usbc,moved leds,added gnd zone,fixed some routing
